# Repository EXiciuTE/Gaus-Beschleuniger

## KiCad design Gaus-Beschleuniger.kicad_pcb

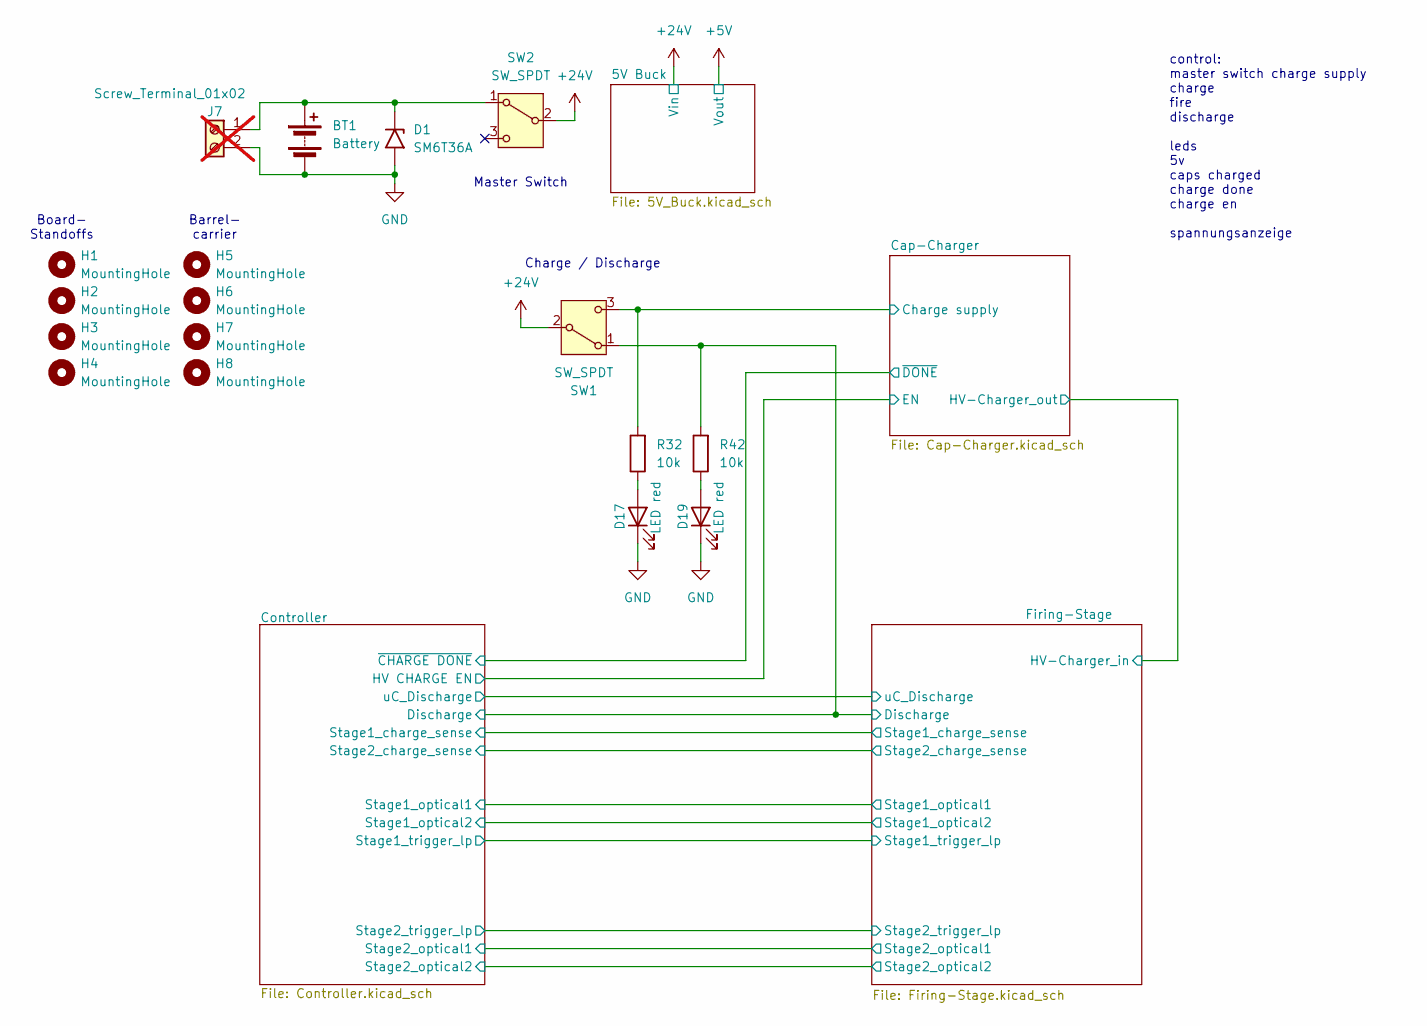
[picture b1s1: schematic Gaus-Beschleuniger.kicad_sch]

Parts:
BT1: Battery; AMASS_XT60-M_1x02_P7.20mm_Vertical; LCSC_Part_# C5334533
D1: SM6T36A; D_SMB; MPN SM6T36A; LCSC_Part_# C7436537
D17, D19: LED red; LED_D5.0mm; MPN 151051RS11000
H1, H2, H3, H4: MountingHole; MountingHole_4.3mm_M4_DIN965
H5, H6, H7, H8: MountingHole; MountingHole_3.2mm_M3_DIN965
J7: Screw_Terminal_01x02; TerminalBlock_Phoenix_MKDS-1,5-2-5.08_1x02_P5.08mm_Horizont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; not fitted
R32, R42: 10k; R_0805_2012Metric_Pad1.20x1.40mm_HandSolder; MPN RC0805FR-0710KL; LCSC_Part_# C84376
SW1, SW2: SW_SPDT; Toggle_Switch_SPDT_PCB; MPN SW-T2-2E-A-A2-M1; LCSC_Part_# C4950128

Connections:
+24V: SW1.2 (B), SW2.2 (B); also elsewhere on the board
/Cap-Charger/Charge supply: R32.2, SW1.3 (C); also elsewhere on the board
/Controller/Discharge: R42.2, SW1.1 (A); also elsewhere on the board
GND: BT1.2 (-), D1.2 (A2), D17.1 (K), D19.1 (K), J7.2; also elsewhere on the board
unnamed: BT1.1 (+), D1.1 (A1), J7.1, SW2.1 (A)
unnamed: D17.2 (A), R32.1
unnamed: D19.2 (A), R42.1

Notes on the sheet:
Board- Standoffs
control: master switch charge supply charge fire discharge leds 5v caps charged charge done charge en spannungsanzeige
Master Switch
Barrel- carrier
Charge / Discharge

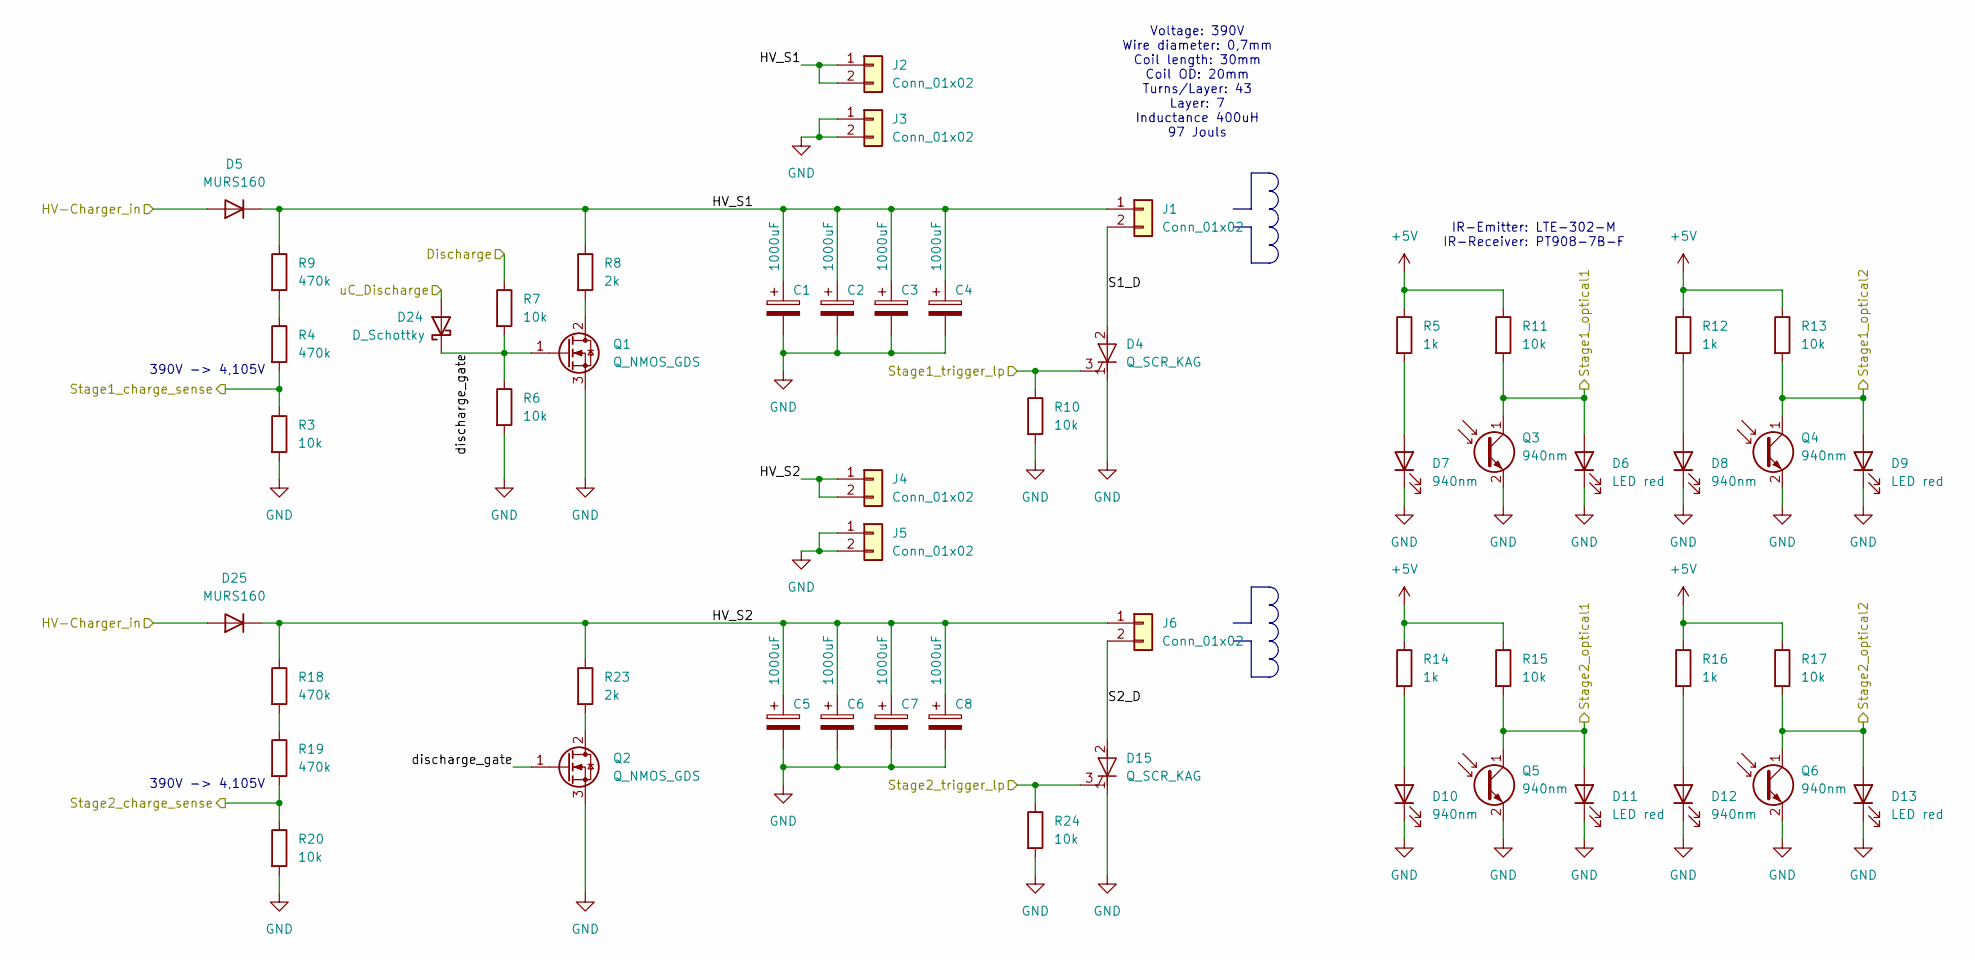
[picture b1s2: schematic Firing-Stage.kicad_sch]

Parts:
C1, C2, C3, C4, C5, C6, C7, C8: 1000uF; CP_Radial_D35.0mm_P10.00mm_SnapIn; MPN ESMR401VSN102MA50S; LCSC_Part_# C1589731
D4, D15: Q_SCR_KAG; TO-247-3_Horizontal_TabDown; MPN 70TPS12; LCSC_Part_# C335786
D5, D25: MURS160; D_SMB_Handsoldering; MPN MURS160; LCSC_Part_# C16378
D6, D9, D11, D13: LED red; LED_D5.0mm; MPN 151051RS11000
D7, D8, D10, D12: 940nm; LED_SideEmitter_Rectangular_W4.5mm_H1.6mm; MPN LTE-302-M; LCSC_Part_# C6980548
D24: D_Schottky; D_SOD-123; MPN B0540W-7-F; LCSC_Part_# C154764
J1, J6: Conn_01x02; SolderWire-1sqmm_1x02_P5.4mm_D1.4mm_OD2.7mm
J2, J3, J4, J5: Conn_01x02; PinHeader_1x02_P2.54mm_Vertical
Q1, Q2: Q_NMOS_GDS; SOT-223-3_TabPin2; MPN IPN60R3K4CEATMA1
Q3, Q4, Q5, Q6: 940nm; Osram_LPT80A; MPN PT908-7B-F; LCSC_Part_# C17179478
R3, R6, R7, R10, R11, R13, R15, R17, R20, R24: 10k; R_0805_2012Metric_Pad1.20x1.40mm_HandSolder; MPN RC0805FR-0710KL; LCSC_Part_# C84376
R4, R9, R18, R19: 470k; R_Axial_DIN0207_L6.3mm_D2.5mm_P10.16mm_Horizontal; MPN RNV14FAL470K; LCSC_Part_# C2642472
R5, R12, R14, R16: 1k; R_0805_2012Metric_Pad1.20x1.40mm_HandSolder; MPN RC0805FR-101KL; LCSC_Part_# C5842544
R8, R23: 2k; R_Axial_Power_L48.0mm_W12.5mm_P60.96mm; MPN SQP10AJB-2K; LCSC_Part_# C20166277

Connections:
+5V: R5.1, R11.1, R12.1, R13.1, R14.1, R15.1, R16.1, R17.1; also elsewhere on the board
/Cap-Charger/HV-Charger_out: D5.2 (A), D25.2 (A); also elsewhere on the board
/Controller/Discharge: R7.1; also elsewhere on the board
/Controller/Stage1_charge_sense: R3.1, R4.2; also elsewhere on the board
/Controller/Stage1_optical1: D6.2 (A), Q3.1 (C), R11.2; also elsewhere on the board
/Controller/Stage1_optical2: D9.2 (A), Q4.1 (C), R13.2; also elsewhere on the board
/Controller/Stage1_trigger_lp: D4.3 (G), R10.1; also elsewhere on the board
/Controller/Stage2_charge_sense: R19.2, R20.1; also elsewhere on the board
/Controller/Stage2_optical1: D11.2 (A), Q5.1 (C), R15.2; also elsewhere on the board
/Controller/Stage2_optical2: D13.2 (A), Q6.1 (C), R17.2; also elsewhere on the board
/Controller/Stage2_trigger_lp: D15.3 (G), R24.1; also elsewhere on the board
/Controller/uC_Discharge: D24.2 (A); also elsewhere on the board
/Firing-Stage/HV_S1: C1.1, C2.1, C3.1, C4.1, D5.1 (K), J1.1, J2.1, J2.2, R8.1, R9.1
/Firing-Stage/HV_S2: C5.1, C6.1, C7.1, C8.1, D25.1 (K), J4.1, J4.2, J6.1, R18.1, R23.1
/Firing-Stage/S1_D: D4.2 (A), J1.2
/Firing-Stage/S2_D: D15.2 (A), J6.2
/Firing-Stage/discharge_gate: D24.1 (K), Q1.1 (G), Q2.1 (G), R6.1, R7.2
GND: C1.2, C2.2, C3.2, C4.2, C5.2, C6.2, C7.2, C8.2, D4.1 (K), D6.1 (K), D7.1 (K), D8.1 (K), D9.1 (K), D10.1 (K), D11.1 (K), D12.1 (K), D13.1 (K), D15.1 (K), J3.1, J3.2, J5.1, J5.2, Q1.3 (S), Q2.3 (S), Q3.2 (E), Q4.2 (E), Q5.2 (E), Q6.2 (E), R3.2, R6.2, R10.2, R20.2, R24.2; also elsewhere on the board
unnamed: D7.2 (A), R5.2
unnamed: D8.2 (A), R12.2
unnamed: D10.2 (A), R14.2
unnamed: D12.2 (A), R16.2
unnamed: Q1.2 (D), R8.2
unnamed: Q2.2 (D), R23.2
unnamed: R4.1, R9.2
unnamed: R18.2, R19.1

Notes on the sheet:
IR-Emitter: LTE-302-M IR-Receiver: PT908-7B-F
Voltage: 390V Wire diameter: 0,7mm Coil length: 30mm Coil OD: 20mm Turns/Layer: 43 Layer: 7 Inductance 400uH 97 Jouls
390V -> 4,105V

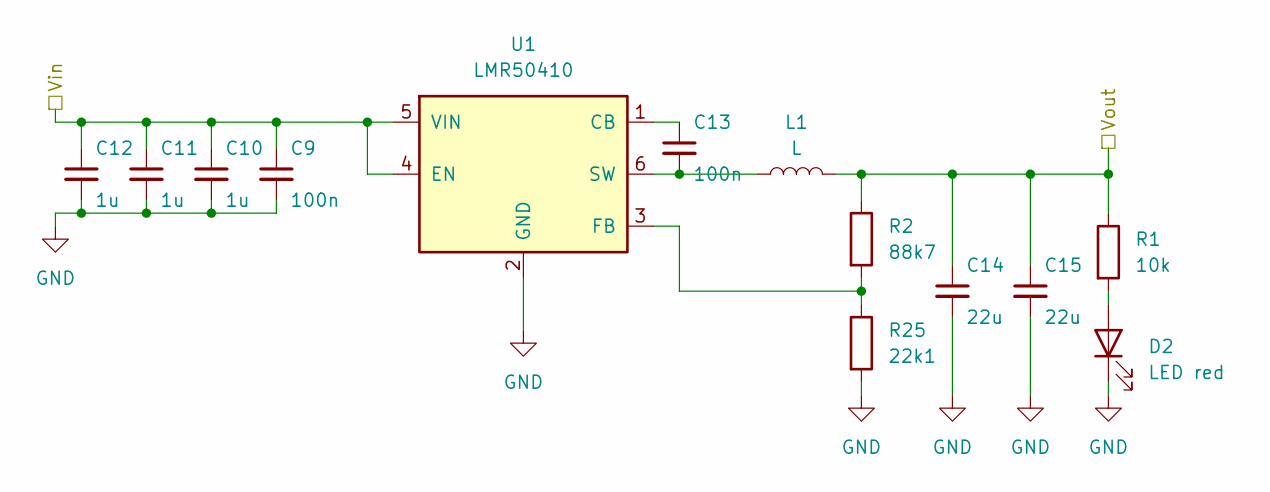
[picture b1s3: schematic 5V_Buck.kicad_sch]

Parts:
C9, C13: 100n; C_0805_2012Metric_Pad1.18x1.45mm_HandSolder; Voltage 100V; MPN CL21B104KCFNNNE; LCSC_Part_# C28233
C10, C11, C12: 1u; C_1206_3216Metric_Pad1.33x1.80mm_HandSolder; Voltage 100V; MPN CL31B105KCHNNNE; LCSC_Part_# C13832
C14, C15: 22u; C_0805_2012Metric_Pad1.18x1.45mm_HandSolder; Voltage 10V; MPN GRM21BR61A226ME44L; LCSC_Part_# C441864
D2: LED red; LED_D5.0mm; MPN 151051RS11000
L1: L; L_Bourns_SRN6045TA; MPN SRN6045-150M; LCSC_Part_# C3224592
R1: 10k; R_0805_2012Metric_Pad1.20x1.40mm_HandSolder; MPN RC0805FR-0710KL; LCSC_Part_# C84376
R2: 88k7; R_0805_2012Metric_Pad1.20x1.40mm_HandSolder; MPN RC0805FR-0788K7L; LCSC_Part_# C273823
R25: 22k1; R_0805_2012Metric_Pad1.20x1.40mm_HandSolder; MPN AC0805FR-0722K1L; LCSC_Part_# C228640
U1: LMR50410; SOT-23-6; MPN LMR50410XDBVR; LCSC_Part_# C2841056

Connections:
+5V: C14.1, C15.1, L1.2, R1.1, R2.1; also elsewhere on the board
+24V: C9.1, C10.1, C11.1, C12.1, U1.4 (EN), U1.5 (VIN); also elsewhere on the board
GND: C9.2, C10.2, C11.2, C12.2, C14.2, C15.2, D2.1 (K), R25.2, U1.2 (GND); also elsewhere on the board
unnamed: D2.2 (A), R1.2
unnamed: C13.1, U1.1 (CB)
unnamed: R2.2, R25.1, U1.3 (FB)
unnamed: C13.2, L1.1, U1.6 (SW)

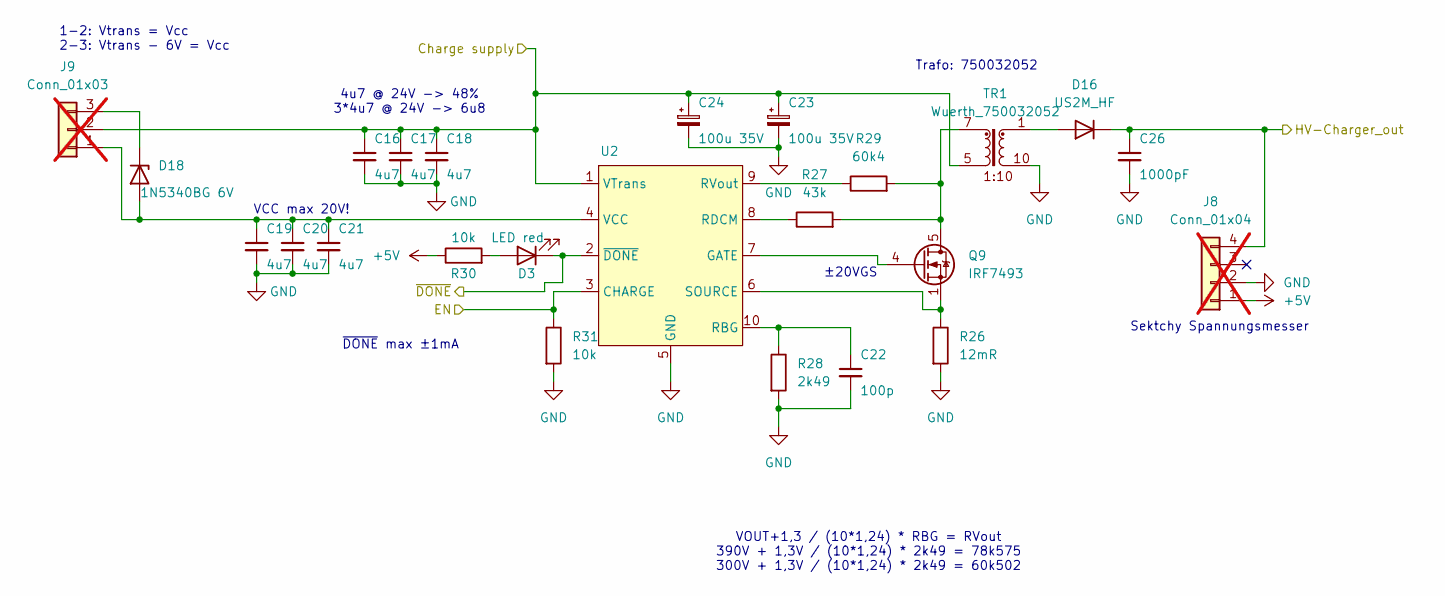
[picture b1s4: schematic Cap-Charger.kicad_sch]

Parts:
C16, C17, C18, C19, C20, C21: 4u7; C_1206_3216Metric_Pad1.33x1.80mm_HandSolder; Voltage 50V; MPN CL31B475KBHNNNE; LCSC_Part_# C51205
C22: 100p; C_0603_1608Metric_Pad1.08x0.95mm_HandSolder; Voltage 50V; MPN C0603C101J5GACTU; LCSC_Part_# C2167328
C23, C24: 100u 35V; CP_Radial_D6.3mm_P2.50mm; MPN 35ZLH100MEFC6.3X11; LCSC_Part_# C109392
C26: 1000pF; C_1206_3216Metric_Pad1.33x1.80mm_HandSolder; Voltage 1000V; MPN CC1206KKX7RDBB102; LCSC_Part_# C23631
D3: LED red; LED_D5.0mm; MPN 151051RS11000
D16: US2M_HF; D_SMB_Handsoldering; Voltage 1000V; MPN US2M_HF; LCSC_Part_# C17247425
D18: 1N5340BG 6V; D_DO-201_P15.24mm_Horizontal; MPN 1N5340BG; LCSC_Part_# C232444
J8: Conn_01x04; PinHeader_1x04_P2.54mm_Vertical; not fitted
J9: Conn_01x03; PinHeader_1x03_P2.54mm_Vertical; not fitted
Q9: IRF7493; SOIC-8_3.9x4.9mm_P1.27mm; MPN IRF7493; LCSC_Part_# C13914
R26: 12mR; R_1206_3216Metric_Pad1.30x1.75mm_HandSolder; MPN PA1206FRE7W0R012Z; LCSC_Part_# C7023635
R27: 43k; R_0603_1608Metric_Pad0.98x0.95mm_HandSolder; MPN RC0603FR-0743KL; LCSC_Part_# C137719
R28: 2k49; R_0603_1608Metric_Pad0.98x0.95mm_HandSolder; MPN RC0603FR-132K49L; LCSC_Part_# C4210186
R29: 60k4; R_0603_1608Metric_Pad0.98x0.95mm_HandSolder; MPN RC0603FR-0760K4L; LCSC_Part_# C165742
R30, R31: 10k; R_0805_2012Metric_Pad1.20x1.40mm_HandSolder; MPN RC0805FR-0710KL; LCSC_Part_# C84376
TR1: Wuerth_750032052; T_Wurth_WE-FB3751-EFD20; MPN 750032052
U2: LT3750; MSOP-10_3x3mm_P0.5mm; MPN LT3750; LCSC_Part_# C580129

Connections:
+5V: J8.1, R30.1; also elsewhere on the board
/Cap-Charger/Charge supply: C16.1, C17.1, C18.1, C23.1, C24.1, J9.2, TR1.4, TR1.5, U2.1 (VTrans); also elsewhere on the board
/Cap-Charger/EN: R31.1, U2.3 (CHARGE); also elsewhere on the board
/Cap-Charger/HV-Charger_out: C26.1, D16.1 (K), J8.4; also elsewhere on the board
/Cap-Charger/~DONE: D3.1 (K), U2.2 (~DONE); also elsewhere on the board
GND: C16.2, C17.2, C18.2, C19.2, C20.2, C21.2, C22.2, C23.2, C24.2, C26.2, J8.2, R26.2, R28.2, R31.2, TR1.10, U2.5 (GND); also elsewhere on the board
unnamed: D3.2 (A), R30.2
unnamed: D16.2 (A), TR1.1
unnamed: C19.1, C20.1, C21.1, D18.2 (A), J9.1, U2.4 (VCC)
unnamed: D18.1 (K), J9.3
unnamed: Q9.5 (D), Q9.6 (D), Q9.7 (D), Q9.8 (D), R27.2, R29.2, TR1.6, TR1.7
unnamed: Q9.4 (G), U2.7 (GATE)
unnamed: C22.1, R28.1, U2.10 (RBG)
unnamed: R27.1, U2.8 (RDCM)
unnamed: R29.1, U2.9 (RVout)
unnamed: Q9.1 (S), Q9.2 (S), Q9.3 (S), R26.1, U2.6 (SOURCE)

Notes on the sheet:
1-2: Vtrans = Vcc 2-3: Vtrans - 6V = Vcc
~{DONE} max ±1mA
VCC max 20V!
±20VGS
VOUT+1,3 / (10*1,24) * RBG = RVout 390V + 1,3V / (10*1,24) * 2k49 = 78k575 300V + 1,3V / (10*1,24) * 2k49 = 60k502
4u7 @ 24V -> 48% 3*4u7 @ 24V -> 6u8
Trafo: 750032052
Sektchy Spannungsmesser

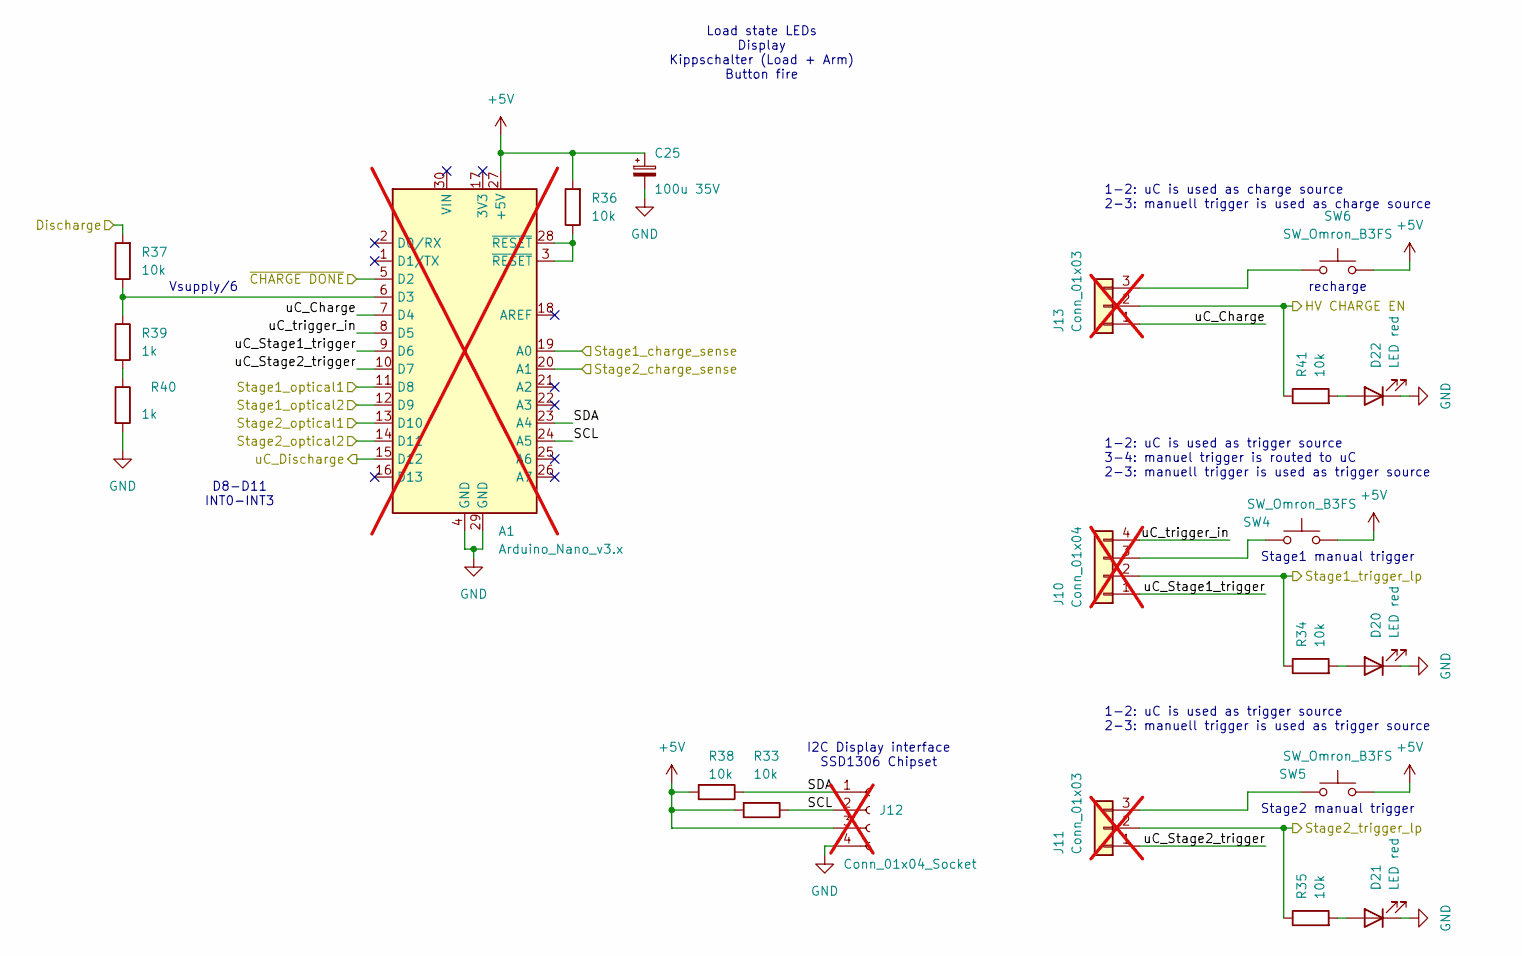
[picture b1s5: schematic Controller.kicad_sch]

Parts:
A1: Arduino_Nano_v3.x; Arduino_Nano; not fitted
C25: 100u 35V; CP_Radial_D6.3mm_P2.50mm; MPN 35ZLH100MEFC6.3X11; LCSC_Part_# C109392
D20, D21, D22: LED red; LED_D5.0mm; MPN 151051RS11000
J10: Conn_01x04; PinHeader_1x04_P2.54mm_Vertical; not fitted
J11, J13: Conn_01x03; PinHeader_1x03_P2.54mm_Vertical; not fitted
J12: Conn_01x04_Socket; PinSocket_1x04_P2.54mm_Vertical; not fitted
R33, R34, R35, R36, R37, R38, R41: 10k; R_0805_2012Metric_Pad1.20x1.40mm_HandSolder; MPN RC0805FR-0710KL; LCSC_Part_# C84376
R39, R40: 1k; R_0805_2012Metric_Pad1.20x1.40mm_HandSolder; MPN RC0805FR-101KL; LCSC_Part_# C5842544
SW4, SW5, SW6: SW_Omron_B3FS; SW_TH_Tactile_Omron_B3F-10xx; MPN B3F-1000; LCSC_Part_# C93157

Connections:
+5V: A1.27 (+5V), C25.1, J12.3, R33.2, R36.2, R38.2, SW4.2, SW5.2, SW6.2; also elsewhere on the board
/Cap-Charger/EN: J13.2, R41.1; also elsewhere on the board
/Cap-Charger/~DONE: A1.5 (D2); also elsewhere on the board
/Controller/Discharge: R37.2; also elsewhere on the board
/Controller/SCL: A1.24 (A5), J12.2, R33.1
/Controller/SDA: A1.23 (A4), J12.1, R38.1
/Controller/Stage1_charge_sense: A1.19 (A0); also elsewhere on the board
/Controller/Stage1_optical1: A1.11 (D8); also elsewhere on the board
/Controller/Stage1_optical2: A1.12 (D9); also elsewhere on the board
/Controller/Stage1_trigger_lp: J10.2, R34.1; also elsewhere on the board
/Controller/Stage2_charge_sense: A1.20 (A1); also elsewhere on the board
/Controller/Stage2_optical1: A1.13 (D10); also elsewhere on the board
/Controller/Stage2_optical2: A1.14 (D11); also elsewhere on the board
/Controller/Stage2_trigger_lp: J11.2, R35.1; also elsewhere on the board
/Controller/uC_Charge: A1.7 (D4), J13.1
/Controller/uC_Discharge: A1.15 (D12); also elsewhere on the board
/Controller/uC_Stage1_trigger: A1.9 (D6), J10.1
/Controller/uC_Stage2_trigger: A1.10 (D7), J11.1
/Controller/uC_trigger_in: A1.8 (D5), J10.4
GND: A1.4 (GND), A1.29 (GND), C25.2, D20.1 (K), D21.1 (K), D22.1 (K), J12.4, R40.2; also elsewhere on the board
unnamed: A1.6 (D3), R37.1, R39.1
unnamed: A1.3 (~RESET), A1.28 (~RESET), R36.1
unnamed: D20.2 (A), R34.2
unnamed: D21.2 (A), R35.2
unnamed: D22.2 (A), R41.2
unnamed: J10.3, SW4.1
unnamed: J11.3, SW5.1
unnamed: J13.3, SW6.1
unnamed: R39.2, R40.1

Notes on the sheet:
Vsupply/6
1-2: uC is used as charge source 2-3: manuell trigger is used as charge source
1-2: uC is used as trigger source 2-3: manuell trigger is used as trigger source
recharge
D8-D11 INT0-INT3
1-2: uC is used as trigger source 3-4: manuel trigger is routed to uC 2-3: manuell trigger is used as trigger source
Stage1 manual trigger
Stage2 manual trigger
I2C Display interface SSD1306 Chipset
Load state LEDs Display Kippschalter (Load + Arm) Button fire

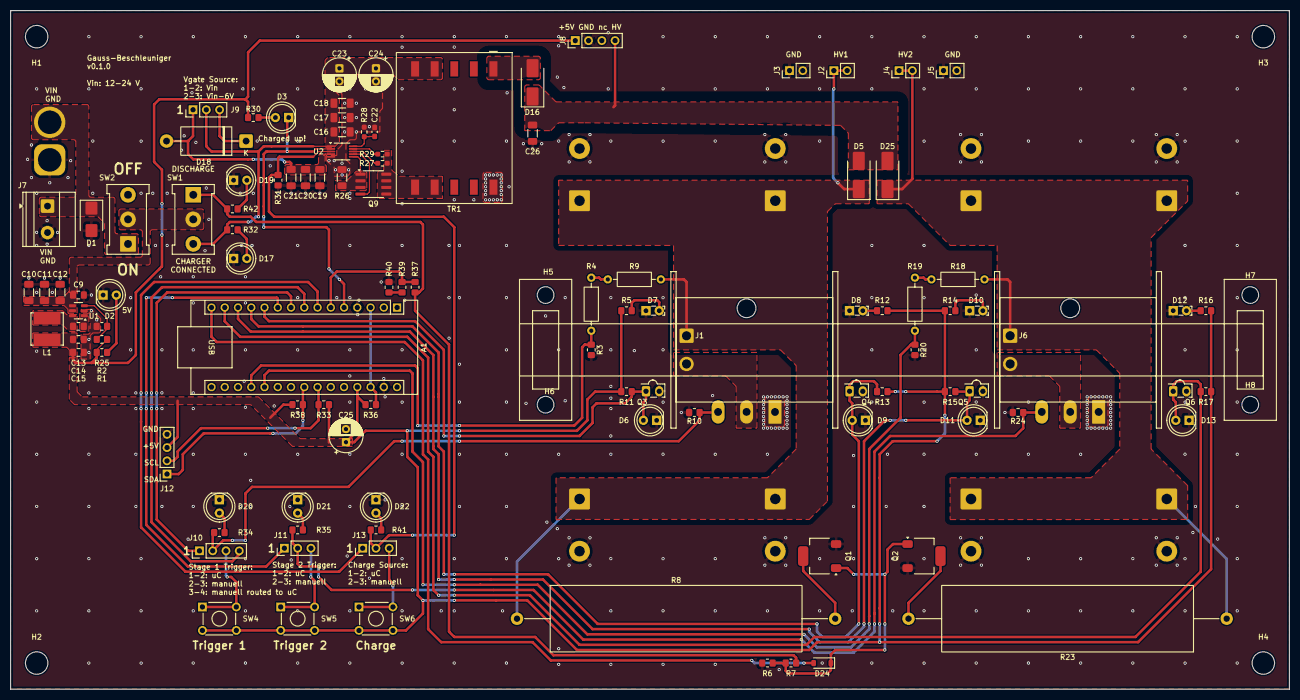
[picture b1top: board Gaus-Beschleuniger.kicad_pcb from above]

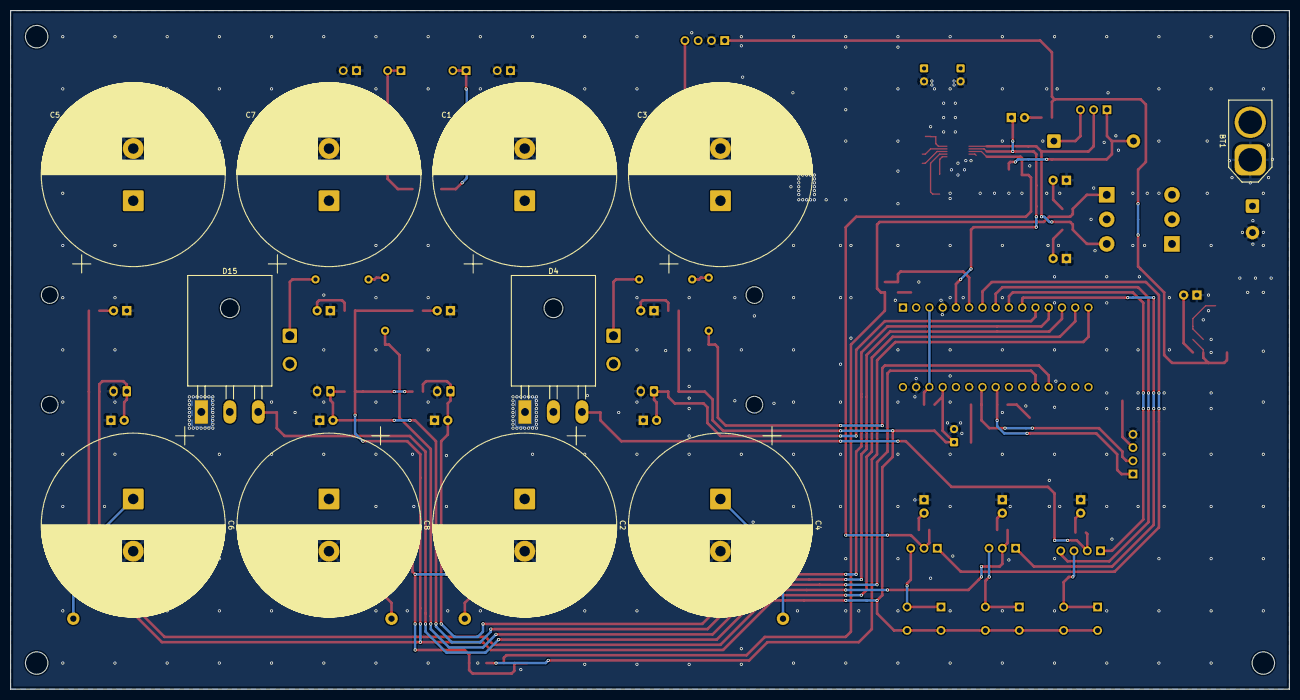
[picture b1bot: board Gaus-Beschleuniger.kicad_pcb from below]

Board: 2 copper layers, 245.0 x 130.0 mm, 128 parts (11 on the bottom side), 62 nets.

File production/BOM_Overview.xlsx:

Reference | Qty | Value | Footprint | Voltage | MPN | LCSC_Part_# | STATUS
A1 | 1 | Arduino_Nano_v3.x | Module:Arduino_Nano |  |  |  | home
BT1 | 1 | Battery | Connector_AMASS:AMASS_XT60-M_1x02_P7.20mm_Vertical |  |  | C5334533 | home
C1,C2,C3,C4,C5,C6,C7,C8 | 8 | 1000uF | Capacitor_THT:CP_Radial_D35.0mm_P10.00mm_SnapIn |  | ESMR401VSN102MA50S | C1589731 | digikey
C9,C13 | 2 | 100n | Capacitor_SMD:C_0805_2012Metric_Pad1.18x1.45mm_HandSolder | 100V | CL21B104KCFNNNE | C28233 | PCBA
C10,C11,C12 | 3 | 1u | Capacitor_SMD:C_1206_3216Metric_Pad1.33x1.80mm_HandSolder | 100V | CL31B105KCHNNNE | C13832 | PCBA
C14,C15 | 2 | 22u | Capacitor_SMD:C_0805_2012Metric_Pad1.18x1.45mm_HandSolder | 10V | GRM21BR61A226ME44L | C441864 | PCBA
C16,C17,C18,C19,C20,C21 | 6 | 4u7 | Capacitor_SMD:C_1206_3216Metric_Pad1.33x1.80mm_HandSolder | 50V | CL31B475KBHNNNE | C51205 | PCBA
C22 | 1 | 100p | Capacitor_SMD:C_0603_1608Metric_Pad1.08x0.95mm_HandSolder | 50V | C0603C101J5GACTU | C2167328 | digikey
C23,C24,C25 | 3 | 100u 35V | Capacitor_THT:CP_Radial_D6.3mm_P2.50mm |  | 35ZLH100MEFC6.3X11 | C109392 | PCBA
C26 | 1 | 1000pF | Capacitor_SMD:C_1206_3216Metric_Pad1.33x1.80mm_HandSolder | 1000V | CC1206KKX7RDBB102 | C23631 | digikey
D1 | 1 | SM6T36A | Diode_SMD:D_SMB |  | SM6T36A | C7436537 | digikey
D2,D3,D6,D9,D11,D13,D17,D19,D20,D21,D22 | 11 | LED red | LED_THT:LED_D5.0mm |  | 151051RS11000 |  | digikey
D4,D15 | 2 | Q_SCR_KAG | Package_TO_SOT_THT:TO-247-3_Horizontal_TabDown |  | 70TPS12 | C335786 | home
D5,D25 | 2 | MURS160 | Diode_SMD:D_SMB_Handsoldering |  | MURS160 | C16378 | PCBA
D7,D8,D10,D12 | 4 | 940nm | LED_THT:LED_SideEmitter_Rectangular_W4.5mm_H1.6mm |  | LTE-302-M | C6980548 | digikey
D16 | 1 | US2M_HF | Diode_SMD:D_SMB_Handsoldering | 1000V | US2M_HF | C17247425 | digikey
D18 | 1 | 1N5340BG 6V | Diode_THT:D_DO-201_P15.24mm_Horizontal |  | 1N5340BG | C232444 | digikey
D24 | 1 | D_Schottky | Diode_SMD:D_SOD-123 |  | B0540W-7-F | C154764 | digikey
J1,J2,J3,J4,J5,J6 | 6 | Conn_01x02 | Connector_PinHeader_2.54mm:PinHeader_1x02_P2.54mm_Vertical,Connector_Wire:Solde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 |  |  |  | home
J7 | 1 | Screw_Terminal_01x02 | TerminalBlock_Phoenix:TerminalBlock_Phoenix_MKDS-1,5-2-5.08_1x02_P5.08mm_Horizo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 |  |  |  | home
J8,J10 | 2 | Conn_01x04 | Connector_PinHeader_2.54mm:PinHeader_1x04_P2.54mm_Vertical |  |  |  | home
J9,J11,J13 | 3 | Conn_01x03 | Connector_PinHeader_2.54mm:PinHeader_1x03_P2.54mm_Vertical |  |  |  | home
J12 | 1 | Conn_01x04_Socket | Connector_PinSocket_2.54mm:PinSocket_1x04_P2.54mm_Vertical |  |  |  | home
L1 | 1 | L | Inductor_SMD:L_Bourns_SRN6045TA |  | SRN6045-150M | C3224592 | digikey
Q1,Q2 | 2 | Q_NMOS_GDS | Package_TO_SOT_SMD:SOT-223-3_TabPin2 |  | IPN60R3K4CEATMA1 |  | digikey
Q3,Q4,Q5,Q6 | 4 | 940nm | OptoDevice:Osram_LPT80A |  | PT908-7B-F | C17179478 | digikey
Q9 | 1 | IRF7493 | Package_SO:SOIC-8_3.9x4.9mm_P1.27mm |  | IRF7493 | C13914 | digikey
R1,R3,R6,R7,R10,R11,R13,R15,R17,R20,R24,R30,R31,R32,R33,R34,R35,R36,R37,R38,R41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 | 22 | 10k | Resistor_SMD:R_0805_2012Metric_Pad1.20x1.40mm_HandSolder |  | RC0805FR-0710KL | C84376 | PCBA
R2 | 1 | 88k7 | Resistor_SMD:R_0805_2012Metric_Pad1.20x1.40mm_HandSolder |  | RC0805FR-0788K7L | C273823 | PCBA
R4,R9,R18,R19 | 4 | 470k | Resistor_THT:R_Axial_DIN0207_L6.3mm_D2.5mm_P10.16mm_Horizontal |  | RNV14FAL470K | C2642472 | digikey
R5,R12,R14,R16,R39,R40 | 6 | 1k | Resistor_SMD:R_0805_2012Metric_Pad1.20x1.40mm_HandSolder |  | RC0805FR-101KL | C5842544 | digikey
R8,R23 | 2 | 2k | Resistor_THT:R_Axial_Power_L48.0mm_W12.5mm_P60.96mm |  | SQP10AJB-2K | C20166277 | digikey
R25 | 1 | 22k1 | Resistor_SMD:R_0805_2012Metric_Pad1.20x1.40mm_HandSolder |  | AC0805FR-0722K1L | C228640 | PCBA
R26 | 1 | 12mR | Resistor_SMD:R_1206_3216Metric_Pad1.30x1.75mm_HandSolder |  | PA1206FRE7W0R012Z | C7023635 | digikey
R27 | 1 | 43k | Resistor_SMD:R_0603_1608Metric_Pad0.98x0.95mm_HandSolder |  | RC0603FR-0743KL | C137719 | PCBA
R28 | 1 | 2k49 | Resistor_SMD:R_0603_1608Metric_Pad0.98x0.95mm_HandSolder |  | RC0603FR-132K49L | C4210186 | digikey
R29 | 1 | 60k4 | Resistor_SMD:R_0603_1608Metric_Pad0.98x0.95mm_HandSolder |  | RC0603FR-0760K4L | C165742 | PCBA
SW1,SW2 | 2 | SW_SPDT | 00_Library:Toggle_Switch_SPDT_PCB |  | SW-T2-2E-A-A2-M1 | C4950128 | digikey
SW4,SW5,SW6 | 3 | SW_Omron_B3FS | Button_Switch_THT:SW_TH_Tactile_Omron_B3F-10xx |  | B3F-1000 | C93157 | digikey
TR1 | 1 | Wuerth_750032052 | 00_Library:T_Wurth_WE-FB3751-EFD20 |  | 750032052 |  | digikey
U1 | 1 | LMR50410 | Package_TO_SOT_SMD:SOT-23-6 |  | LMR50410XDBVR | C2841056 | PCBA
U2 | 1 | LT3750 | Package_SO:MSOP-10_3x3mm_P0.5mm |  | LT3750 | C580129 | PCBA
Display | 1 |  |  |  |  | Kosten
Spannungsanzeige | 1 |  |  |  |  | PCB+PCBA | 110 | mit allem
 |  |  |  |  |  | Digikey
 |  |  |  |  |  | Aliexpress

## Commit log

2025-11-15 init commit - schematic nearly done
2025-11-17 rough placement
2025-11-18 start layout
2025-11-19 layout weiter
2025-11-19 firing routing, uC routing done
2025-11-20 placement and routing done drc errors, stiching vias and polish next
2025-11-21 Layout finished
2025-11-21 now with gerber files :)
2025-11-21 reorganize
2025-11-22 update fab files ;/
